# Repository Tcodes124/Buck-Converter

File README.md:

# Buck-Converter
AlphaF is the external footprint library imported from SnapMagic and UltraLibrarian
Alpha is the external imported symbol library
*Both these libraries are named so that they appear at the top of the library list for ease of use

The BOM.csv is an exact quantity of all parts with no extra parts.

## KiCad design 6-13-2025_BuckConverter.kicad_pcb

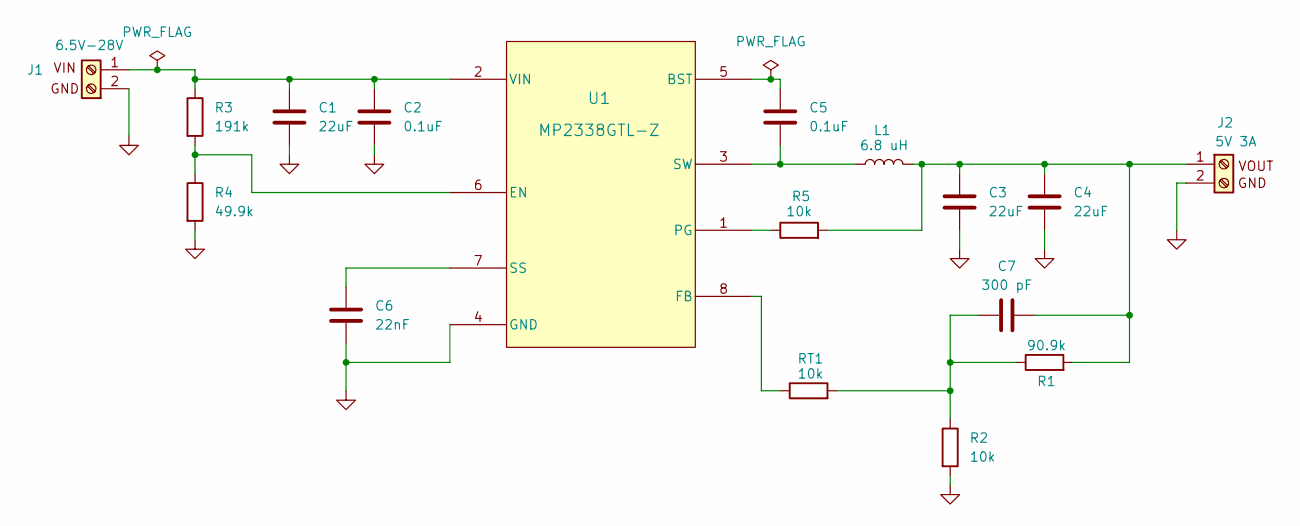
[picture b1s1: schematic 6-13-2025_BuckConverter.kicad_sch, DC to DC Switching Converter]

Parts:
C1, C3, C4: 22uF; C_0805_2012Metric_Pad1.18x1.45mm_HandSolder
C2, C5: 0.1uF; C_0805_2012Metric_Pad1.18x1.45mm_HandSolder
C6: 22nF; C_0805_2012Metric_Pad1.18x1.45mm_HandSolder
C7: 300 pF; C_0805_2012Metric_Pad1.18x1.45mm_HandSolder
J1: 6V to 35V; TERM BLK 2POS SIDE ENTRY
J2: 5V 3A; TERM BLK 2POS SIDE ENTRY
L1: 6.8 uH; FIXED IND 6.8UH 4.5A
R1: 90.9k; R_0805_2012Metric_Pad1.20x1.40mm_HandSolder
R2, R5: 10k; R_0805_2012Metric_Pad1.20x1.40mm_HandSolder
R3: 191k; R_0805_2012Metric_Pad1.20x1.40mm_HandSolder
R4: 49.9k; R_0805_2012Metric_Pad1.20x1.40mm_HandSolder
RT1: 10k; R_0805_2012Metric_Pad1.20x1.40mm_HandSolder
U1: MP2338GTL-Z; SOT583_MP2338_MNP-L

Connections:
GND: C1.2, C2.2, C3.2, C4.2, C6.2, J1.2 (GND), J2.2 (GND), R2.2, R4.2, U1.4 (GND)
unnamed: C7.1, R1.1, R2.1, RT1.2
unnamed: C1.1, C2.1, J1.1 (VIN), R3.1, U1.2 (VIN)
unnamed: C3.1, C4.1, C7.2, J2.1 (VIN), L1.2, R1.2, R5.2
unnamed: C5.1, U1.5 (BST)
unnamed: R3.2, R4.1, U1.6 (EN)
unnamed: RT1.1, U1.8 (FB)
unnamed: R5.1, U1.1 (PG)
unnamed: C6.1, U1.7 (SS)
unnamed: C5.2, L1.1, U1.3 (SW)

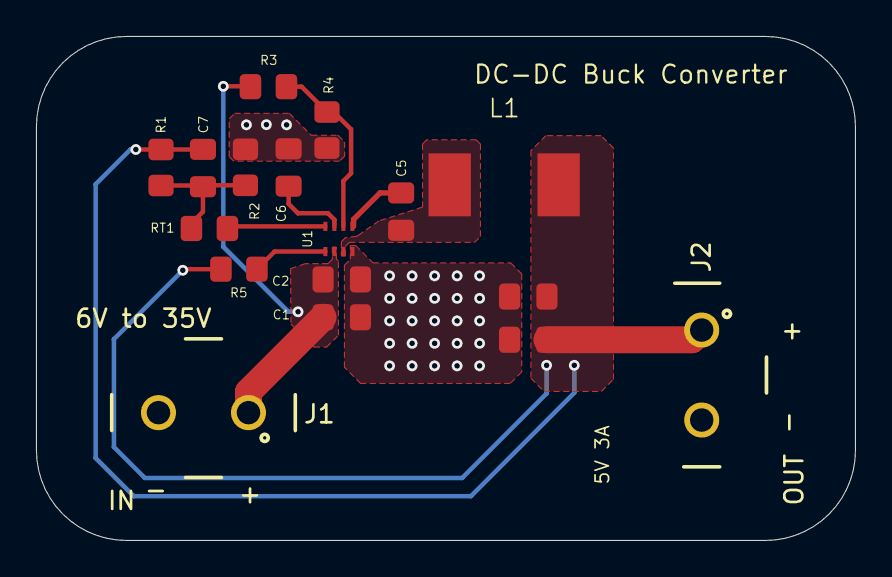
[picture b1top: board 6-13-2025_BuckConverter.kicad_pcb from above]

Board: 2 copper layers, 45.5 x 28.0 mm, 17 parts (0 on the bottom side), 10 nets.

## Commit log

2025-06-22 Update LICENSE
2025-06-22 Includes completed schematic and started PCB placement.
2025-06-22 Updated PCB placement
2025-06-23 Completed PCB layout and routing.
2025-06-24 Updated PCB layout, generated prototype gerber and drill files.
2025-06-25 Updated directory name and schematic requirments.
2025-06-27 Finalized layout and generated manufacturing files.
